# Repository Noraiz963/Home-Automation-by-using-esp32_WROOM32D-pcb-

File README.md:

# ESP32 Home Automation — 2-Channel Mains Relay Controller

A mains-powered, WiFi/Bluetooth-enabled 2-channel relay controller designed in KiCad, built around the **ESP32-WROOM-32**. Designed for switching mains-connected loads (lights, appliances, etc.) with manual switch override, status LEDs, and a dedicated UART header for programming and debugging.

## Why This Exists

Home automation projects need a safe, reliable way to let a microcontroller switch mains-voltage loads without exposing the low-voltage logic circuitry to mains hazards or noise. This board handles that end-to-end: an isolated AC-DC module supplies clean low-voltage power, optocouplers electrically isolate the ESP32 from the relay/mains side, and flyback-protected relays do the actual switching — all while exposing manual switch inputs and a UART header for flashing and debugging without a dedicated USB-serial chip onboard.

## Circuit Overview

- **Power supply**: Mains AC input (J2) → HLK-PM01 isolated AC-DC module (5V) → AMS1117-3.3 linear regulator (3.3V) for ESP32 and logic
- **Core MCU**: ESP32-WROOM-32 (U1) — WiFi/Bluetooth microcontroller driving all logic, relay control, and connectivity
- **Relay channels (x2)**: GPIO → NPN transistor (Q1/Q2) → PC817 optocoupler (U2/U3) → relay coil (K1/K2), with 1N4148 flyback diodes (D2/D4) for coil protection
- **Status LEDs**: LED1/LED2 driven from ESP32 GPIOs through current-limiting resistors
- **UART header (J1)**: 3.3V/RXD/TXD/GND — for external USB-to-UART programmer/debugger
- **Switch input (J3)**: External manual switch inputs (IN1/IN2) for local override control
- **Reset & Boot (SW1/SW2)**: Manual boot-mode and reset buttons with pull-up resistors, standard for ESP32 flashing workflow

## Signal Flow (Concept)

**Power path:**
1. Mains AC enters via J2 (L/N).
2. HLK-PM01 isolates and converts mains AC directly to 5V DC — a safety-isolated, self-contained module (no custom transformer/rectifier design needed).
3. AMS1117-3.3 regulates the 5V down to a clean 3.3V rail, filtered by C1/C2, to power the ESP32 and logic-side components.
4. L1/L2 provide EMI filtering on the incoming mains lines.

**Relay switching path (per channel):**
1. ESP32 GPIO (IN1 or IN2) drives a current-limiting resistor into the base of an NPN transistor (Q1/Q2).
2. The transistor switches current through a PC817 optocoupler's internal LED.
3. The optocoupler's output drives the relay coil circuit — this is the critical **isolation boundary** between the low-voltage ESP32 logic and the mains-connected relay/load side.
4. The relay coil energizes, mechanically switching its contacts to connect mains L1/L2 to the output screw terminal (the load).
5. A flyback diode (1N4148) across the coil absorbs the voltage spike generated when the coil de-energizes, protecting the driving transistor from damage.

**Programming/debug path:**
- J1 exposes 3.3V, RXD, TXD, GND for an external USB-to-UART adapter.
- SW1 ("boot") pulls ESP32's IO0 low to enter flashing/bootloader mode.
- SW2 ("ENB") pulls EN low to reset the chip.
- R7/R8 pull-ups hold both lines high during normal operation.

**Manual override path:**
- J3 provides external switch inputs (IN1/IN2), allowing physical switches to control relay state independent of WiFi/app-based control — useful as a local override or fallback if connectivity is lost.

**Status indication:**
- LED1/LED2, driven from dedicated ESP32 GPIOs, can be used in firmware to indicate relay state, WiFi connection status, or general system status.

**Ground referencing:**
- Care should be taken that the low-voltage logic-side GND and mains-side relay contacts remain properly isolated per the PC817 optocouplers — the optical isolation is what keeps the ESP32 and any connected programmer safe from mains-side faults.

## Schematic
)

## PCB Layout

## 3D Render

## Bill of Materials

| Ref | Component | Value / Part |
|-----|-----------|--------------|
| U1 | Microcontroller Module | ESP32-WROOM-32 |
| U4 | Linear Regulator | AMS1117-3.3 |
| U6 | Isolated AC-DC Module | HLK-PM01 |
| U2, U3 | Optocoupler | PC817 |
| K2 | Relay | PR13-5V-450-1C |
| K1 | Relay | RAYEX-L90AS |
| Q1, Q2 | NPN Transistor | S8050 |
| D2, D4 | Diode (flyback) | 1N4148 |
| D1 | Status LED | — |
| LED1, LED2 | Status LEDs | — |
| R1, R2 | Resistor (transistor base) | 1kΩ |
| R3, R4 | Resistor (optocoupler output) | 1kΩ |
| R5, R6 | Resistor (LED current limit) | 1kΩ |
| R7, R8 | Resistor (boot/reset pull-up) | 10kΩ |
| C1 | Capacitor (regulator input) | 10µF |
| C2 | Capacitor (regulator output) | 22µF |
| L1, L2 | Inductor/Ferrite (EMI filter) | — |
| J1 | UART Header (4-pin) | 3.3V / RXD / TXD / GND |
| J2 | Mains Input (Screw Terminal, 4-pin) | AC L/N |
| J3 | Switch Input (Screw Terminal, 3-pin) | IN1 / IN2 / GND |
| SW1 | Push Button (Boot) | — |
| SW2 | Push Button (Reset/EN) | — |

## Pin Reference

### J1 — UART (Programming/Debug)
| Pin | Signal |
|---|---|
| 1 | 3.3V |
| 2 | RXD |
| 3 | TXD |
| 4 | GND |

### J3 — Switch Input
| Pin | Signal |
|---|---|
| 1 | IN1 |
| 2 | IN2 |
| 3 | GND |

## Features

- Two independently controlled relay channels for switching mains-connected loads
- Optically isolated relay drive circuitry for safety between logic and mains sides
- Onboard isolated AC-DC power supply — no external power adapter required
- Manual switch input for local override control
- Dedicated UART header for firmware flashing/debugging (no onboard USB, keep an external USB-UART adapter handy)
- Manual boot/reset buttons for standard ESP32 flashing workflow
- Status LEDs for visual system feedback
- Mounting holes for enclosure integration

## Getting Started

1. Wire mains AC to J2 (L/N) — **use extreme caution; this board has mains-voltage sections. Ensure proper enclosure and isolation before powering on.**
2. Connect an external USB-to-UART adapter to J1 (3.3V, RXD, TXD, GND).
3. Hold **SW1 (boot)**, tap **SW2 (reset)**, then release SW1 to enter flashing mode.
4. Flash your firmware (e.g., via Arduino IDE, ESP-IDF, or ESPHome).
5. Connect loads to the relay output screw terminals.
6. Optionally wire physical switches to J3 for manual override control.

## Tools Used
- KiCad 10.0.4 (schematic capture, PCB layout, 3D visualization)

## Status
Completed schematic and PCB layout design; 3D render verified.

## Safety Notice

⚠️ This board includes mains-voltage circuitry. Improper assembly, wiring, or enclosure design can result in electric shock or fire hazard. Ensure proper isolation clearances, use an appropriately rated enclosure, and follow local electrical safety codes. Do not operate this board without proper enclosure while connected to mains power.

## Notes
Built as a home automation project combining ESP32 WiFi connectivity with safe, isolated mains relay switching — designed for controlling lights or appliances with both remote (WiFi/app) and local (manual switch) control options.

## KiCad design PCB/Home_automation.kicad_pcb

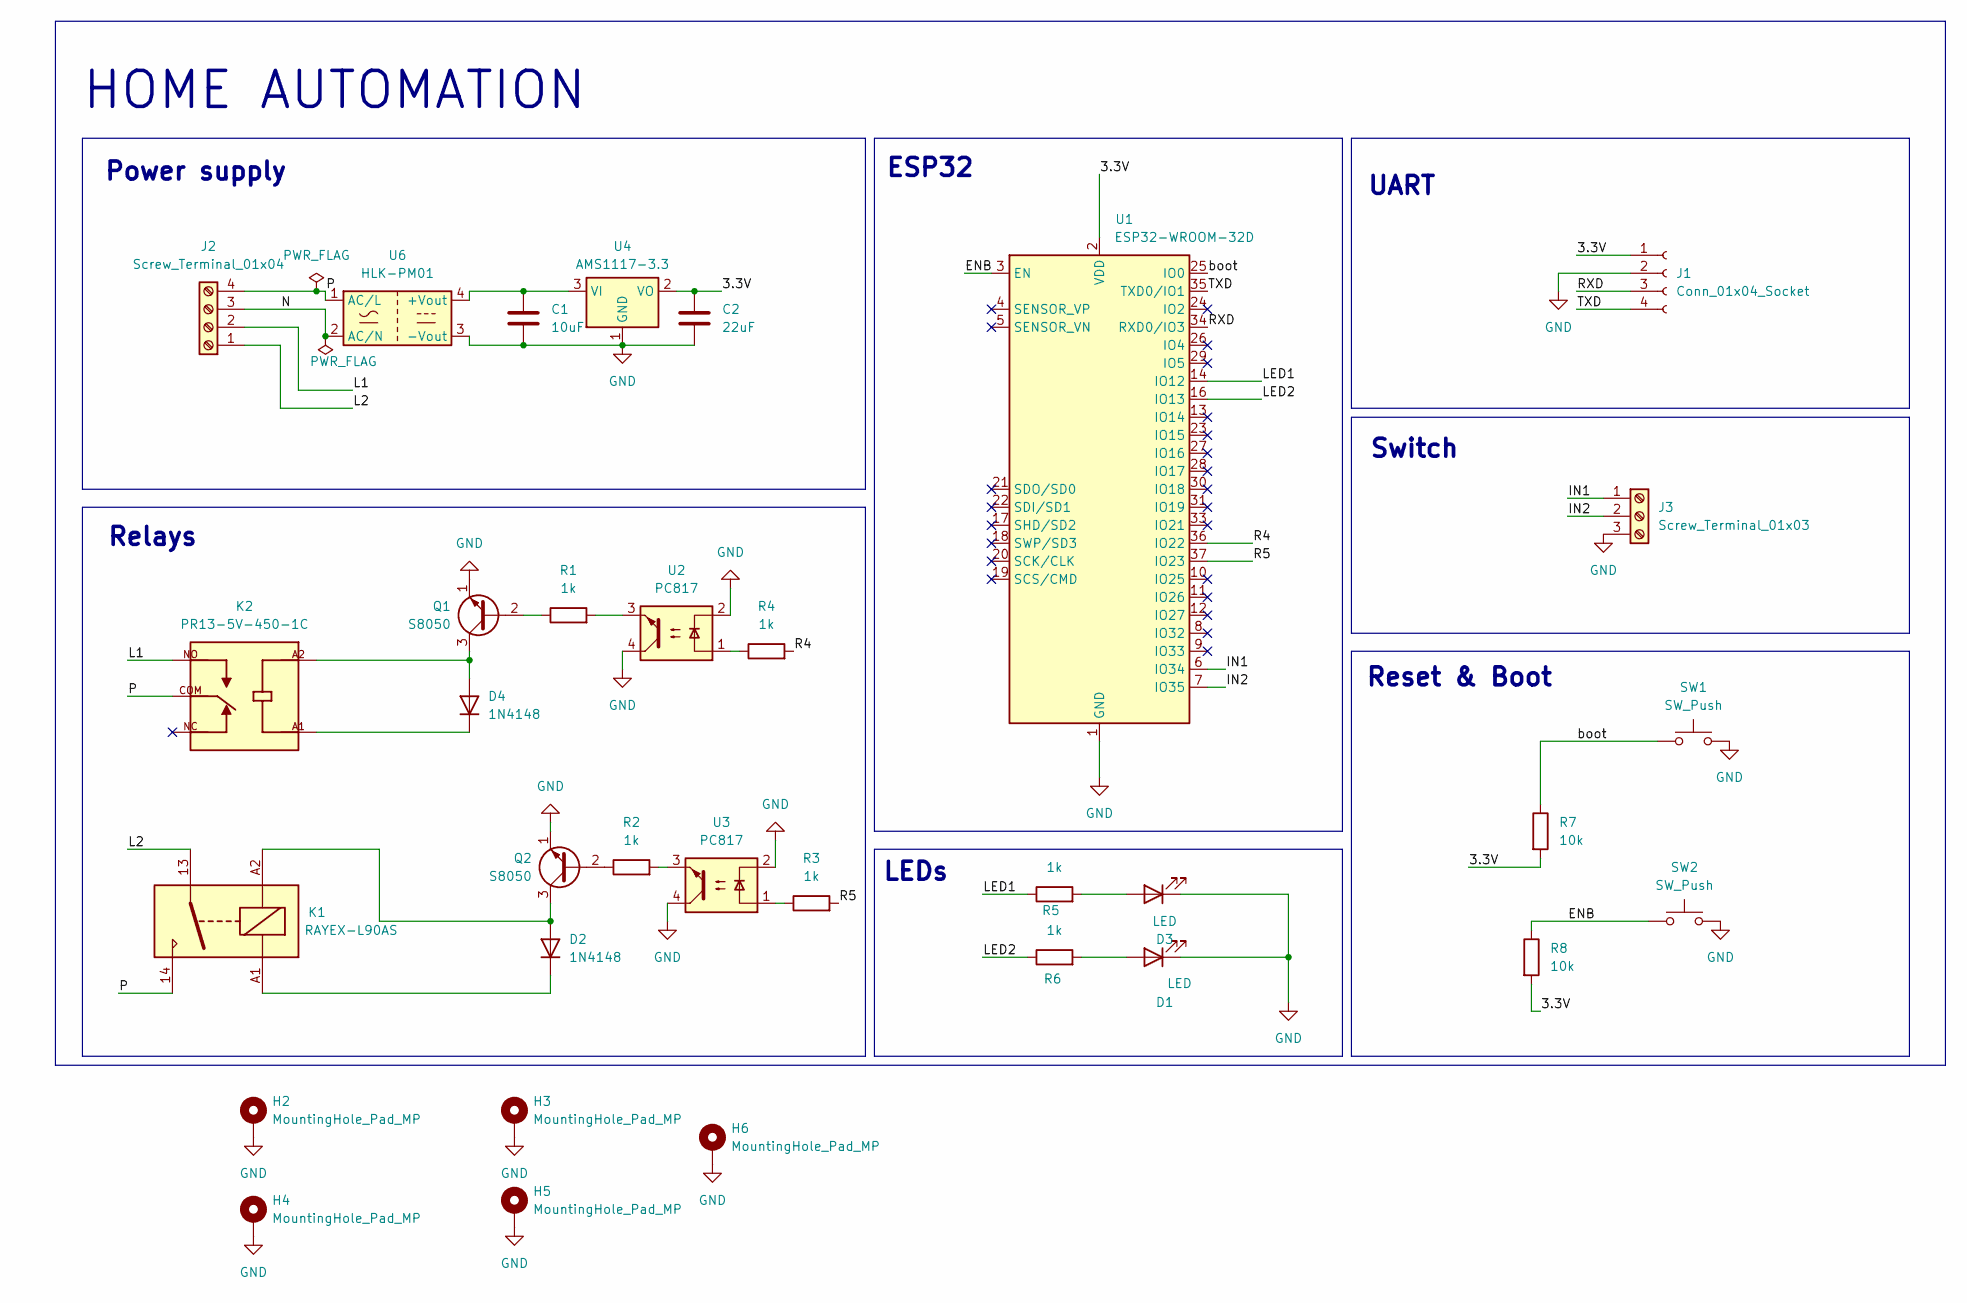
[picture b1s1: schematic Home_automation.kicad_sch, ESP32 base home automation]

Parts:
C1: 10uF; C_0805_2012Metric
C2: 22uF; C_0805_2012Metric
D1, D3: LED; LED_0805_2012Metric
D2, D4: 1N4148; D_DO-35_SOD27_P7.62mm_Horizontal
H2, H3, H4, H5, H6: MountingHole_Pad_MP; MountingHole_2.7mm_M2.5_Pad_Via
J1: Conn_01x04_Socket; PinSocket_1x04_P2.54mm_Vertical_SMD_Pin1Right
J2: Screw_Terminal_01x04; TerminalBlock_MaiXu_MX126-5.0-04P_1x04_P5.00mm
J3: Screw_Terminal_01x03; TerminalBlock_MaiXu_MX126-5.0-03P_1x03_P5.00mm
K1: RAYEX-L90AS; Relay_SPST_RAYEX-L90AS
K2: PR13-5V-450-1C; RELAY_PR13-5V-450-1C; PARTREV 1.0
Q1, Q2: S8050; TO-92_Inline
R1, R2, R3, R4, R5, R6: 1k; R_0805_2012Metric
R7, R8: 10k; R_0805_2012Metric
SW1, SW2: SW_Push; SW_PUSH_6mm
U1: ESP32-WROOM-32D
U2, U3: PC817; DIP-4_W7.62mm
U4: AMS1117-3.3; SOT-223-3_TabPin2
U6: HLK-PM01; Converter_ACDC_Hi-Link_HLK-PMxx

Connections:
/3.3V: C2.1, J1.1, R7.2, R8.2, U1.2 (VDD), U4.2 (VO)
/ENB: R8.1, SW2.1, U1.3 (EN)
/IN1: J3.1, U1.6 (IO34)
/IN2: J3.2, U1.7 (IO35)
/L1: J2.2, K2.NO
/L2: J2.1, K1.13
/LED1: R5.1, U1.14 (IO12)
/LED2: R6.1, U1.16 (IO13)
/N: J2.3, U6.2 (AC/N)
/P: J2.4, K1.14, K2.COM, U6.1 (AC/L)
/R4: R4.2, U1.36 (IO22)
/R5: R3.2, U1.37 (IO23)
/RXD: J1.3, U1.34 (RXD0/IO3)
/TXD: J1.4, U1.35 (TXD0/IO1)
/boot: R7.1, SW1.1, U1.25 (IO0)
GND: C1.2, C2.2, D1.1 (K), D3.1 (K), H2.MP, H3.MP, H4.MP, H5.MP, H6.MP, J1.2, J3.3, Q1.1 (E), Q2.1 (E), SW1.2, SW2.2, U1.1 (GND), U1.15 (GND), U1.38 (GND), U1.39 (GND), U2.2, U2.4, U3.2, U3.4, U4.1 (GND), U6.3 (-Vout)
unnamed: D1.2 (A), R6.2
unnamed: D2.2 (A), K1.A2, Q2.3 (C)
unnamed: D2.1 (K), K1.A1
unnamed: D3.2 (A), R5.2
unnamed: D4.2 (A), K2.A2, Q1.3 (C)
unnamed: D4.1 (K), K2.A1
unnamed: Q1.2 (B), R1.1
unnamed: Q2.2 (B), R2.1
unnamed: R1.2, U2.3
unnamed: R2.2, U3.3
unnamed: R3.1, U3.1
unnamed: R4.1, U2.1
unnamed: C1.1, U4.3 (VI), U6.4 (+Vout)

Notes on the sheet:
ESP32
Reset & Boot
Switch
Relays
UART
LEDs
Power supply
HOME AUTOMATION

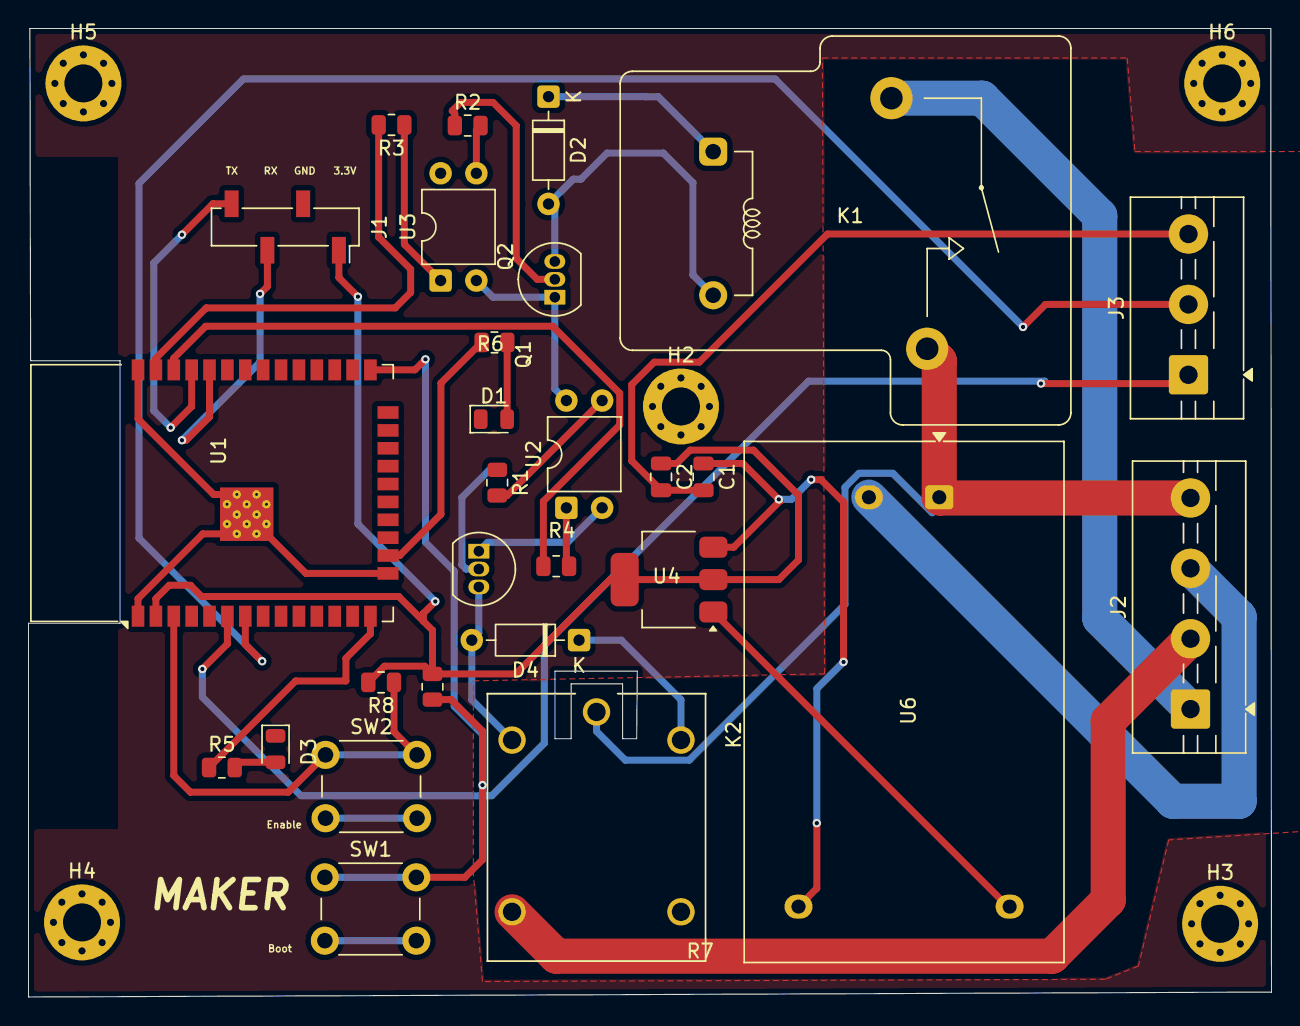
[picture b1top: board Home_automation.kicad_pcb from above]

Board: 2 copper layers, 88.3 x 68.8 mm, 33 parts (0 on the bottom side), 29 nets.
